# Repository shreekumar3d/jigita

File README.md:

# Jig It !

Ease PCB assembly with 3D printed jigs. Achieve perfectly aligned connectors, with no special motor skills!

JigIt is licensed under the AGPL 3.0 License. If you work with electronics, it can
help you save time, material and money. Should you find value in this tool, the
author implores you to take on the moral obligation of abiding by the
"Equal Opportunity" manifesto. Details of what "equal opportunity" means and your
obligations are in [this page](EQUAL-OPPORTUNITY.md). Please take a moment to read
it before you start using the software.

Starting with a PCB design, JigIt achieves this workflow:

 1. Create a 3D printable jig design from a PCB design.
 2. Print jig.
 3. Mount components and PCB on jig. If you notice tolerance issues, tweak parameters, goto step 1.
 4. Solder away for perfect results... every time !

Do checkout [this project's hackaday page](https://hackaday.io/project/198409-pcb-assembly-jig-generator)
for stories and updates.

## Demos

There are many ways to use JigIt. Checkout the [demos directory](demos) for details; here are some examples:

[Raspberry Pi Pico/Pico 2](demo/01-rpi-pico-soldering-jig/README.md)

[Pico Glitcher Board](demo/02-pico-glitcher/README.md)

JigIt is generic. Have a crazy board like this ProtoConn to solder ?

See [ProtoCon demo](demo/06-lots-of-connectors/README.md) for the details; the jig would look and work like this:

[Gridfinity Containers for Electronics](demo/05-gridfinity/README.md)

It's not just for soldering - make Gridfinity containers for all your electronic components in a snap:

It can be used for more than electronics too, with just a bit more work.... Here is an example of a gridfinity container holding three allen keys - M2, M3 and M4:

## Getting Started

See the [Getting Started page](doc/GETTING-STARTED.md).

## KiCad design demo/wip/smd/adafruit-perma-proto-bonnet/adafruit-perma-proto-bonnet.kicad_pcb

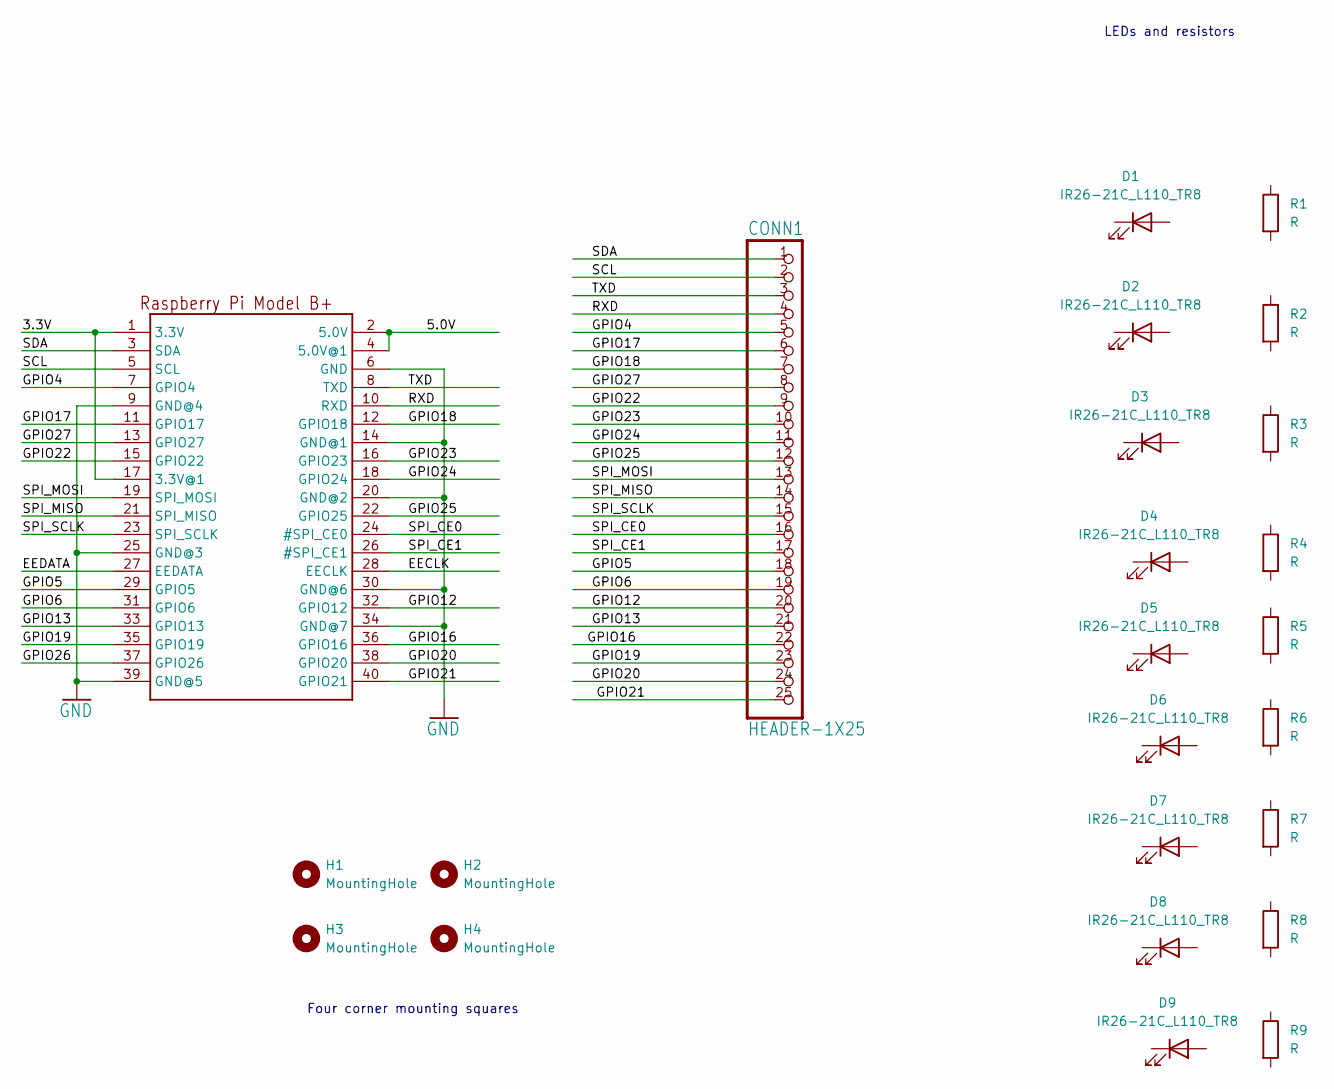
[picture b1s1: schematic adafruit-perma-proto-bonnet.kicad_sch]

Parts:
CONN1: HEADER-1X25; 1X25_ROUND_70MIL
D1, D2, D3, D4, D5, D6, D7, D8, D9: IR26-21C_L110_TR8; LED_1206_3216Metric
H1, H2, H3, H4: MountingHole; MountingHole_2.7mm_M2.5
R1, R2, R3, R4, R5, R6, R7, R8, R9: R; R_1206_3216Metric
RPI1: RASPBERRYPI_BPLUS_BONNETNODIM; PI_BONNET_NODIM

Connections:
/3.3V: RPI1.1 (3.3V), RPI1.17 (3.3V@1)
/5.0V: RPI1.2 (5.0V), RPI1.4 (5.0V@1)
/EECLK: RPI1.28 (EECLK)
/EEDATA: RPI1.27 (EEDATA)
/GPIO4: CONN1.5, RPI1.7 (GPIO4)
/GPIO5: CONN1.18, RPI1.29 (GPIO5)
/GPIO6: CONN1.19, RPI1.31 (GPIO6)
/GPIO12: CONN1.20, RPI1.32 (GPIO12)
/GPIO13: CONN1.21, RPI1.33 (GPIO13)
/GPIO16: CONN1.22, RPI1.36 (GPIO16)
/GPIO17: CONN1.6, RPI1.11 (GPIO17)
/GPIO18: CONN1.7, RPI1.12 (GPIO18)
/GPIO19: CONN1.23, RPI1.35 (GPIO19)
/GPIO20: CONN1.24, RPI1.38 (GPIO20)
/GPIO21: CONN1.25, RPI1.40 (GPIO21)
/GPIO22: CONN1.9, RPI1.15 (GPIO22)
/GPIO23: CONN1.10, RPI1.16 (GPIO23)
/GPIO24: CONN1.11, RPI1.18 (GPIO24)
/GPIO25: CONN1.12, RPI1.22 (GPIO25)
/GPIO26: RPI1.37 (GPIO26)
/GPIO27: CONN1.8, RPI1.13 (GPIO27)
/RXD: CONN1.4, RPI1.10 (RXD)
/SCL: CONN1.2, RPI1.5 (SCL)
/SDA: CONN1.1, RPI1.3 (SDA)
/SPI_CE0: CONN1.16, RPI1.24 (#SPI_CE0)
/SPI_CE1: CONN1.17, RPI1.26 (#SPI_CE1)
/SPI_MISO: CONN1.14, RPI1.21 (SPI_MISO)
/SPI_MOSI: CONN1.13, RPI1.19 (SPI_MOSI)
/SPI_SCLK: CONN1.15, RPI1.23 (SPI_SCLK)
/TXD: CONN1.3, RPI1.8 (TXD)
GND: RPI1.6 (GND), RPI1.9 (GND@4), RPI1.14 (GND@1), RPI1.20 (GND@2), RPI1.25 (GND@3), RPI1.30 (GND@6), RPI1.34 (GND@7), RPI1.39 (GND@5)

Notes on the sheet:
Four corner mounting squares
LEDs and resistors

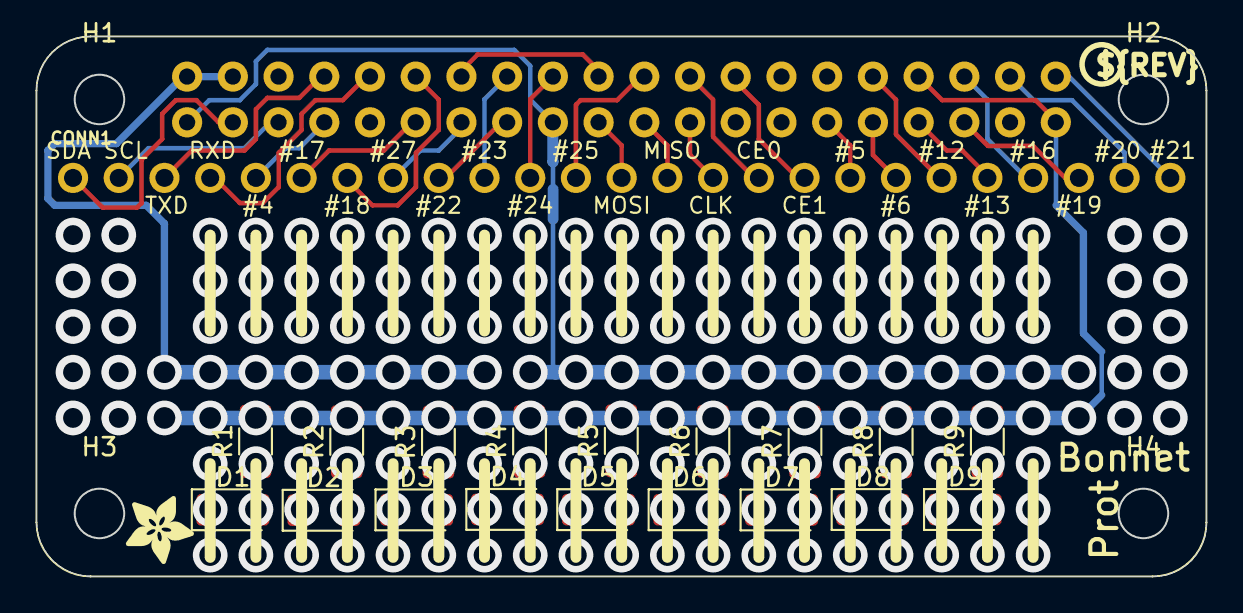
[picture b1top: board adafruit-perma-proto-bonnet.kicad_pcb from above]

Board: 2 copper layers, 65.0 x 30.0 mm, 26 parts (0 on the bottom side), 28 nets.

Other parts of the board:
U1: ADAFRUIT_3.5MM
U3: PCBFEAT-REV-056

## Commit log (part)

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2024-10-22 snippet: Dump points in courtyard
2024-10-22 TH config is now hierarchical, like SMD
    TH.component_shell for generic values
    TH.<ref>.component_shell for overrides
    TH.refs_do_not_process
    TH.refs_only_these
2024-10-23 Beautified preview in oscad,with show/hide options
    PCB, component holders and SMD keepout volumes can be independently
    visualized. These are clearly shown in different colors. It's not
    perfect, but it's pretty good!
    oscad background operator % is used as it allows color control, without
    adding to output geometry. The debug modifier # has a fixed color, so
    not used.
2024-10-23 Component "Volumes" seems better
2024-10-24 Clerer TOML:shell_type,gap,clearence_from_pcb
2024-10-25 --genconfig option to generate starter config file
2024-10-27 Discrete steps for better performance
    Fixed bug where triangles were being skipped. With 0.2mm
    z step I get reasonable, but not perfect results.
    Some artifacts are visible in the final shape - like gaps -
    almost as if something is slipping between the cracks.
2024-10-27 Include missing stp2obj.py
2024-10-28 Good settings for PinHeader_2x10_P2.54mm_Vertical
2024-10-29 Support custom oscad binary and manifold flag.
    Manifold is fast! No need to keep waiting with the old stuff.
2024-10-30 x & y line options for base. Faster prints ahoy
    x_lines and y_lines are new options for the base pattern.
    griddish was a combination of X & Y lines. These are the
    components. They save effectively even more time and material.
    Printing with x/y lines saves about 20 minutes of printing time,
    down from 2 hrs 20 minutes to 2 hrs, compared to griddish. And
    simple lines make it easier for the print head also to move.
2024-10-31 Preparing for license change
2024-10-31 Default shell type is now 'fitting'
    This is robust enough and better results than wiggle. Also, since
    the footprint grouping change, it is no longer possible to change
    all shells in one click. This looks right. If fitting does not
    work for somebody, then they can always fall back to wiggle, or
    even courtyard.
2024-11-01 Autodetect output format
2024-11-01 Moved scad code to gen_scad.py
    Lots of spaghetti code, this is some progress towards cleanup.
2024-11-02 Cosmetic: weird to call a shell 'wiggle'
2024-11-02 Shell type fitting_flowers
    Fitting shells, with thin walls. Shares cuts with "fitting", and
    cuts material and time consumption further. This should benefit
    in cases where the printer can print thinner walls, and when the
    components are large.
2024-11-04 Implement shell_wrapper
    This is basically a wrapper around the shell - thicker than the
    perimeter, but typically not intended to be tall. Both parameters
    are configurable.
    shell_wrapper height includes the base, and its height is independent
    of the mesh line height.
2024-11-04 Hacks: dump pad info in pcb dump
2024-11-04 Initial implementation : Mounting hole spacer jig
    Saves 50% material and 50% time compared to without, for the
    AtiVEGA board.
    Basically for a good height, the jig will just be printing
    vertical shells. This can be substituted by using 3d printed
    spacers. Base layer is still required. The spacer is the
    same shape as the mounting hole outlines.
2024-11-05 Output spacers in place, separable in slicer
    This helps visualize exactly how it is supposed to be used.
    User needs to load object in slicer and select "split to
    objects" (Prusa Slicer) or similar option in other slicers.
    This is also great to overlay onto the step file of the board.
    Zooming in enough will show the gap.
2024-11-05 Delaunay must not include points outside PCB edge
    Mounting holes provided by user can be outside. These will be
    connected to the frame anyway, so no need to add it to delaunay.
    Plus, a bit of -y cleanup. I really need to enforce consistency
    on that one.
2024-11-05 Simple test for component orientation
2024-11-07 Handling of base and wrapper in standalone mode
    Footprints that have more than one 3d model (e.g. Pico, Mini360 etc)
    need extra handling for the base and wrappers. In "jig" mode,
    base is assumed, and things are supposed to be attached in some way
    to the base.
    In standalone mode, that doesn't happen. So the base/wrappers have
    to be generated additionally.
2024-11-07 Fix: bad comparison disabled cut-through shell
    Cut through shells aren't pretty, but yet, let's keep it for now.
2024-11-08 feat:Arrange objects in print bed (xy)
2024-11-12 Minor bug fix
    Missed passing direction. Looks like I didn't test this. Time to
    automate that as well.
2024-11-12 Caching for "body shapes"
    Each component on the board has a "footprint". It can also have
    one/more 3D models, which decide the "shape" of the "body".
    "body" is a new term created here. "body" has a "footprint" and
    a "shape". KiCAD allows you to change the "shape" for every
    "footprint", and it is possible that the user may knowingly or
    unknowingly have slightly different shapes. The tool warns the
2024-11-16 Shapes dont change, default to timestamp for cache
    3D models change very rarely, and most are standard. So, using
    hash(md5sum) is a waste of resources. We default to timestamp. Note
    that just a change in timestamp will invalidate associated shapes.
    This makes for easier testing also (good old 'touch')
2024-11-21 Fix computation of centers. Apply post cache
    Order is important. After I decided to do "rotation is scad"
    (commit : df78c4dfcff42e20485ef45416c1adda98e54e94) this was
    already broken I guess. Didn't notice.
    The change in gen_scad.py is basically unused redundant code.
2024-11-21 Use trimesh module for mesh loading
    trimesh from trimesh.org . This is neat, and provides various
    conveniences we can use - mesh loading, cross sections, various
    mesh ops, etc.
    trimesh itself has various other dependencies, which would hopefully
    not be a deps nightmare. For now, this works for me:
    pip install trimesh[easy]
2024-11-21 Ignore errors while processing Z slices
    Errors are reported. Errors in the mesh cause such errors,
    skipping errors is a reasonable decision, as the rest of the Z
    values may be OK.
2024-11-27 Add equal opportunity blurb.
2024-12-01 More reading for users!
2025-02-22 Fix: ensure no python datatypes goto scad output
    Existing code had numpy float values, which would end up in scad
    output when calling peri_line, resulting in weird output. Convert
    all to float (except scad constants) to eliminate this issue.
    solid python has the provision to create scad "constants" -
    essentially these are arbitrary strings that can be passed
    transparently without evaluation. We use this feature, so this is
2025-02-22 TSSOP20 breakout board design.
    Reverse engineered from off-the-shelf component.
    See README.md for details.
2025-02-23 Adafruit Perma Proto Bonnet, imported to KiCAD 8
    The source is in Eagle:
    https://github.com/adafruit/Adafruit-Perma-Proto-Bonnet-PCB
    This is imported to KiCAD 8. Need this to test SMD LEDs.
2025-02-23 Add test 1206 LED and Resistor in bonnet PCB
2025-02-23 feat:"solid_fill" base type for SMD usage
    Wireframe-ish jigs like what we use with TH components do not
    help keep components in place with a small force.
    With this base type, the entire holding jig becomes solid apart from the
    cut volumes. This gives adequate stiffness to the holding jig.
2025-02-23 Update README, include getting started.
    Clarifies the license on first reading. "Equal opportunity" is
    recommended !
2025-02-24 Handle subprocess differences on Windows
2025-02-25 fix:get --footprint working again
    kicad config parameter had broken it.
2025-02-27 Minor:Include missing change in last commit
2025-03-09 Fix compatibility with FreeCAD 8 built-in python
    FreeCAD 8.0.9 windows installer uses Python 3.11.5. This doesn't
    support delete_on_close arg for tempfile.NamedTemporaryFile().
    We cleanup manually to enhance compatibility and make it usable
    on FreeCAD 8.0.9
2025-03-18 Fix:Decide component is TH using attributes
    SMD components may have TH pads. HasThroughHolePads() is thus
    incorrect.
2025-03-19 Eliminate per component 'delta' values
    Instead, just use the shell values. OpenSCAD customizer now gets
    a "Tune" checkbox per component.
2025-03-19 Moved SMD demos to demo/wip/smd
    Once values are well tuned, plan to move it to demo/smd
2025-03-21 Fix one more np datatype creeping into scad
    Similar to commit b7fb0ad8e6
2025-03-21 Fix bug in groove cutting related to y coords
2025-03-22 Pockets cut through PCB to avoid overhangs
    Sometimes components can straddle the edge of the PCB, or be very
    close to the edge. When pockets don't cut through the PCB,
    some plastic may hang in thin air near the edge. This change
    ensures that all pockets (courtyard, wiggle, fitting and tight)
    cut through the PCB. This is done by increasing the height of the cut
    volume by pcb thickness, and making it begin at z=0.
2025-03-24 "Clearance from PCB" is the right terminology
2025-03-24 Add FOSSDEM Audio Board demo
    Shows off some of the interesting aspects of jigit, and benefits
    of benefits of the sparse structure as opposed to solid jigs.
2025-03-25 New 'wiggle_minus' shell type
    The existing wiggle shell is basically a convex hull, providing a
    loose fit.
    wiggle_minus is wiggle, operating on the potentially concave hull
    created by the "tight" algorithm. This should benefit both front
    and back insertion, as the component can be better constrainted
    in terms of orientation and movement.
2025-03-26 Corrected 2 part jig
    These changes make the 2 part jig a bit chunkier than earlier.
2025-03-27 force_mount option to flexibly place shells in Z
    TH shell with min_z > 0 was taken to be not mounted. This was done
    to process mounted modules such as the Pico on Thejas32.
    force_mount ignores the min_z comparison and includes all models
    in the shell. Doing so changes the meaning of clearance_from_pcb.
    It now cuts from the top of the 3d model, if that has min_z > 0.
    This allows us to cut the top of the shell independent of the
2025-03-28 Improved corner segmentation
    Track cumulative difference in angle to segment corners. Instantaneous
    angle change does not work when finely segmented curves slowly change
    angle; this was causing such lines to be considered one.
    This commit also fixes a bug w.r.t omitting the first and last segmented
    lines.
2025-03-28 Update allen keys demo with cut tight shells
2025-04-02 Demo of ProtoConn with lots of connectors
2025-04-04 Fix:set default display_name to kicad_footprint
2025-04-04 Footprint path convention
    No path is considered as based on kicad share path
    To use a local path, prepend a path
    e.g.
    Diode_THT:D_A-405_P7.62mm_Horizontal is considered from
    KiCAD libraries
    ./ProjectFootprints:CapElectrolytic0 is considered an
2025-04-05 feat:MH based framing for component fitting jig
    Component fitting jigs needs a frame. Use mounting holes (convex
    hull) as that frame.
    Component centers are connected to the frame by default. New config
    option holder.base.minmesh.connect_components_to_frame allows control
    over that.
2025-04-07 SMD clearance mustn't impact MH shells
    SMD clearance cutting into MH shells got in as part of a hack
    done during FOSSHack.
    There's trim volume for that purpose now. That said, might be
    preferable to have a separate mechanism to directly control this.
    There's no reason not to have a separate property controlling this.
2025-04-11 solid base now works with trim below z
    solid is a base style, but it wasn't moving with the trim_below_z
    plane. This commit fixes this. Technically, this implements mesh
    lines that are solid.
    solid base uses the mounting hole frame as the shape for
    component_fitting jigs. For TH_soldering, the PCB edge is used.
    Couple of things to correct later (TODO):
2025-04-13 Clearance for mounting hole shells
    mounting holes shells are distinct compared to component shells.
    Depending on whether they are "in" or "out" of the PCB, they have
    different heights - stretching all the way till the PCB or till
    the top surface. Postive z values work like for component shells,
    negative values extend shells "up"
2025-04-14 fix:don't create islands when MH are outside PCB
    Mounting holes can be outside base volume. Cutting the lines
    creates islands in such cases
2025-04-17 MH ref incl/excl handling, override for shell size
2025-04-18 frame edge must cover all footprints
    Footprints may be outside the hull of the MH, but inside PCB.
    To account for this, we need to consider the hull of MH+footprints
    as the PCB edge.
2025-06-01 Update with demos
